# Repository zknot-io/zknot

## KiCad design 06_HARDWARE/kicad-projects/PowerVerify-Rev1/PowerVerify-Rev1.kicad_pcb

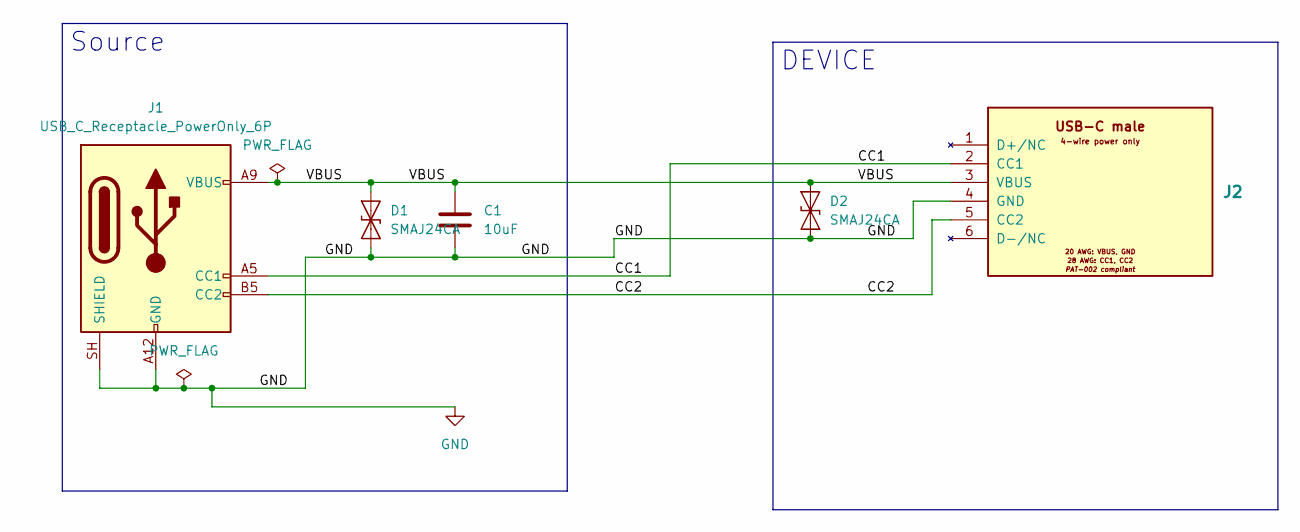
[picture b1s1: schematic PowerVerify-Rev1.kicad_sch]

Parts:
C1: 10uF; C_0805_2012Metric
D1, D2: SMAJ24CA; D_SMA
J1: USB_C_Receptacle_PowerOnly_6P; USB_C_Receptacle_GCT_USB4135-GF-A_6P_TopMnt_Horizontal
J2: Pigtail_USB-C_4wire_ZKNOT; Pigtail_USB-C_4wire_6pad_ZKNOT_THT_Arc; MPN ZKNOT-PGT-USB-C-4W-20AWG-R1

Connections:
/CC1: J1.A5 (CC1), J2.2 (CC1)
/CC2: J1.B5 (CC2), J2.5 (CC2)
/VBUS: C1.2, D1.2 (A2), D2.2 (A2), J1.A9 (VBUS), J1.B9 (VBUS), J2.3 (VBUS)
GND: C1.1, D1.1 (A1), D2.1 (A1), J1.A12 (GND), J1.B12 (GND), J1.SH (SHIELD), J2.4 (GND)

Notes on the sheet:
DEVICE
Source

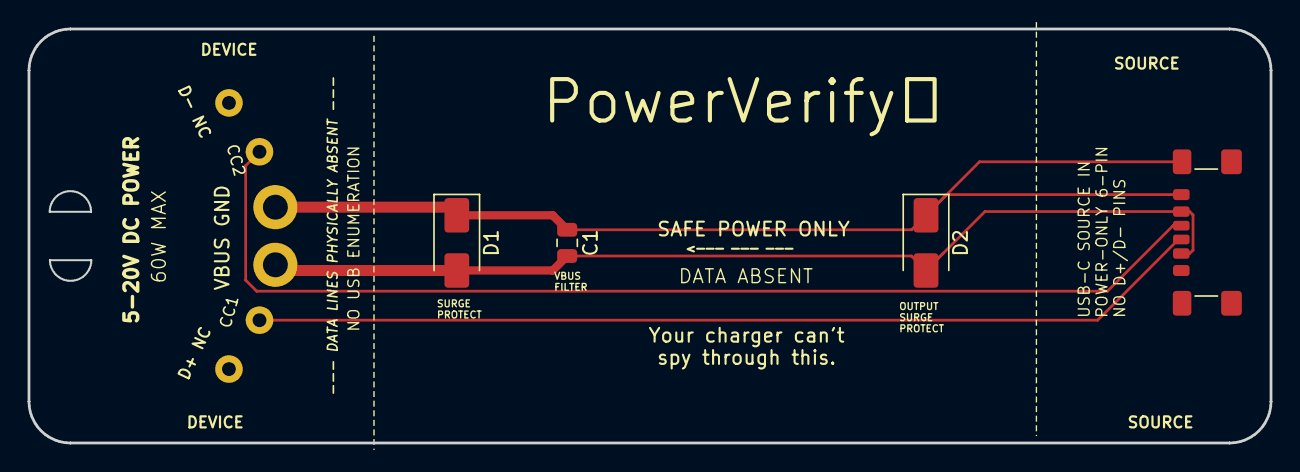
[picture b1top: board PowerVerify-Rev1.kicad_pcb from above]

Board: 2 copper layers, 90.0 x 30.0 mm, 5 parts (0 on the bottom side), 4 nets.

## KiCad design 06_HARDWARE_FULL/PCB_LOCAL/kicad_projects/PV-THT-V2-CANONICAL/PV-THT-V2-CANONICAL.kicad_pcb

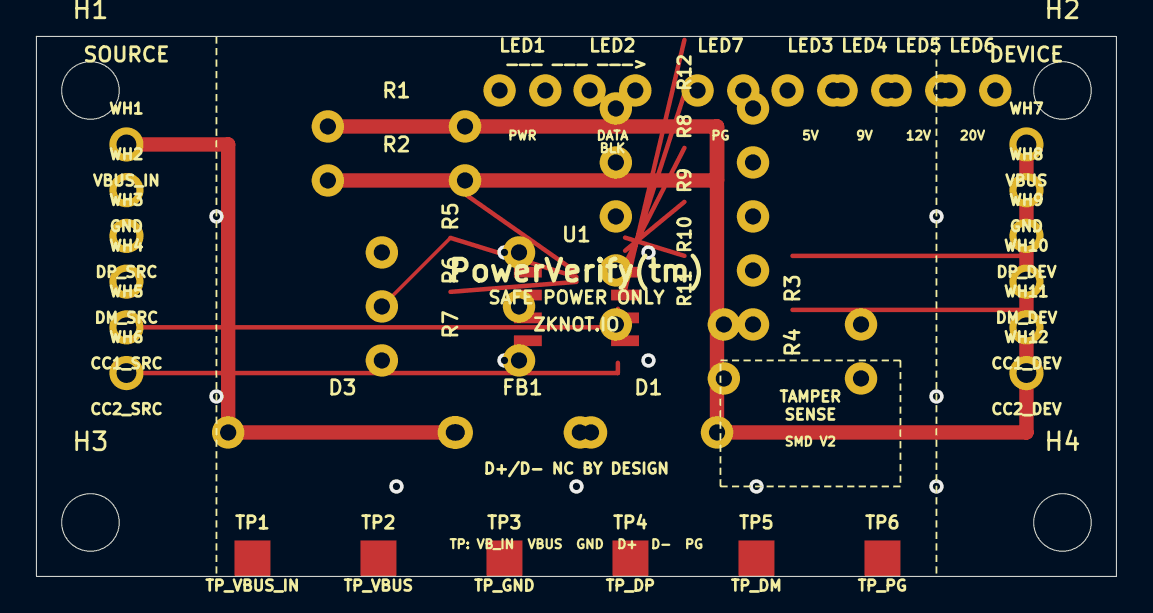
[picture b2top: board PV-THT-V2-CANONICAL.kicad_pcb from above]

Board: 2 copper layers, 60.0 x 30.0 mm, 45 parts (0 on the bottom side), 18 nets.

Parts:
D1: 1N4007; D_DO-41_SOD81_P7.62mm_Horizontal
D3: P6KE5V6A; D_DO-15_P12.70mm_Horizontal
FB1: BLM21PG600SN1D; L_Axial_P7.62mm
H1, H2, H3, H4: MountingHole_M3; MountingHole_3.2mm_M3
LED1: GREEN_PWR; LED_D3.0mm
LED2: RED_DATA_BLK; LED_D3.0mm
LED3: BLUE_5V; LED_D3.0mm
LED4: AMBER_9V; LED_D3.0mm
LED5: ORANGE_12V; LED_D3.0mm
LED6: RED_20V; LED_D3.0mm
LED7: GREEN_PG; LED_D3.0mm
R1, R8, R9, R10, R11, R12: 330; R_Axial_DIN0207_L6.3mm_D2.5mm_P7.62mm_Horizontal
R2: 1k; R_Axial_DIN0207_L6.3mm_D2.5mm_P7.62mm_Horizontal
R3, R4: 5.1k; R_Axial_DIN0207_L6.3mm_D2.5mm_P7.62mm_Horizontal
R5: CFG3_SEL; R_Axial_DIN0207_L6.3mm_D2.5mm_P7.62mm_Horizontal
R6: CFG2_SEL; R_Axial_DIN0207_L6.3mm_D2.5mm_P7.62mm_Horizontal
R7: CFG1_SEL; R_Axial_DIN0207_L6.3mm_D2.5mm_P7.62mm_Horizontal
TP1: TP_VBUS_IN; TestPoint_Pad_2.0x2.0mm
TP2: TP_VBUS; TestPoint_Pad_2.0x2.0mm
TP3: TP_GND; TestPoint_Pad_2.0x2.0mm
TP4: TP_DP; TestPoint_Pad_2.0x2.0mm
TP5: TP_DM; TestPoint_Pad_2.0x2.0mm
TP6: TP_PG; TestPoint_Pad_2.0x2.0mm
U1: CH224K; SOIC-8_3.9x4.9mm_P1.27mm
WH1: VBUS_IN; WireHole_1.1mm
WH2, WH8: GND; WireHole_1.1mm
WH3: DP_SRC; WireHole_1.1mm
WH4: DM_SRC; WireHole_1.1mm
WH5: CC1_SRC; WireHole_1.1mm
WH6: CC2_SRC; WireHole_1.1mm
WH7: VBUS; WireHole_1.1mm
WH9: DP_DEV; WireHole_1.1mm
WH10: DM_DEV; WireHole_1.1mm
WH11: CC1_DEV; WireHole_1.1mm
WH12: CC2_DEV; WireHole_1.1mm

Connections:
CC1_SRC: R3.1, U1.7, WH5.1
CC2_SRC: R4.1, U1.8, WH6.1
CFG1: R7.1, U1.3
CFG2: R6.1, U1.2
CFG3: R5.1, U1.1
DM_SRC: TP5.1, WH4.1
DP_SRC: TP4.1, WH3.1
FLAG_5V: LED3.1, R8.1
FLAG_9V: LED4.1, R9.1
FLAG_12V: LED5.1, R10.1
FLAG_20V: LED6.1, R11.1, U1.6
GND: D3.2, LED1.2, LED2.2, LED3.2, LED4.2, LED5.2, LED6.2, LED7.2, R3.2, R4.2, R5.2, R6.2, R7.2, R8.2, R9.2, R10.2, R11.2, TP3.1, U1.4, WH2.1, WH8.1
LED1_A: LED1.1, R1.2
LED2_A: LED2.1, R2.2
LED7_A: LED7.1, R12.2
PG: R12.1, TP6.1, U1.5
VBUS: D1.2, FB1.2, R1.1, R2.1, TP2.1, WH7.1
VBUS_IN: D1.1, D3.1, FB1.1, TP1.1, WH1.1

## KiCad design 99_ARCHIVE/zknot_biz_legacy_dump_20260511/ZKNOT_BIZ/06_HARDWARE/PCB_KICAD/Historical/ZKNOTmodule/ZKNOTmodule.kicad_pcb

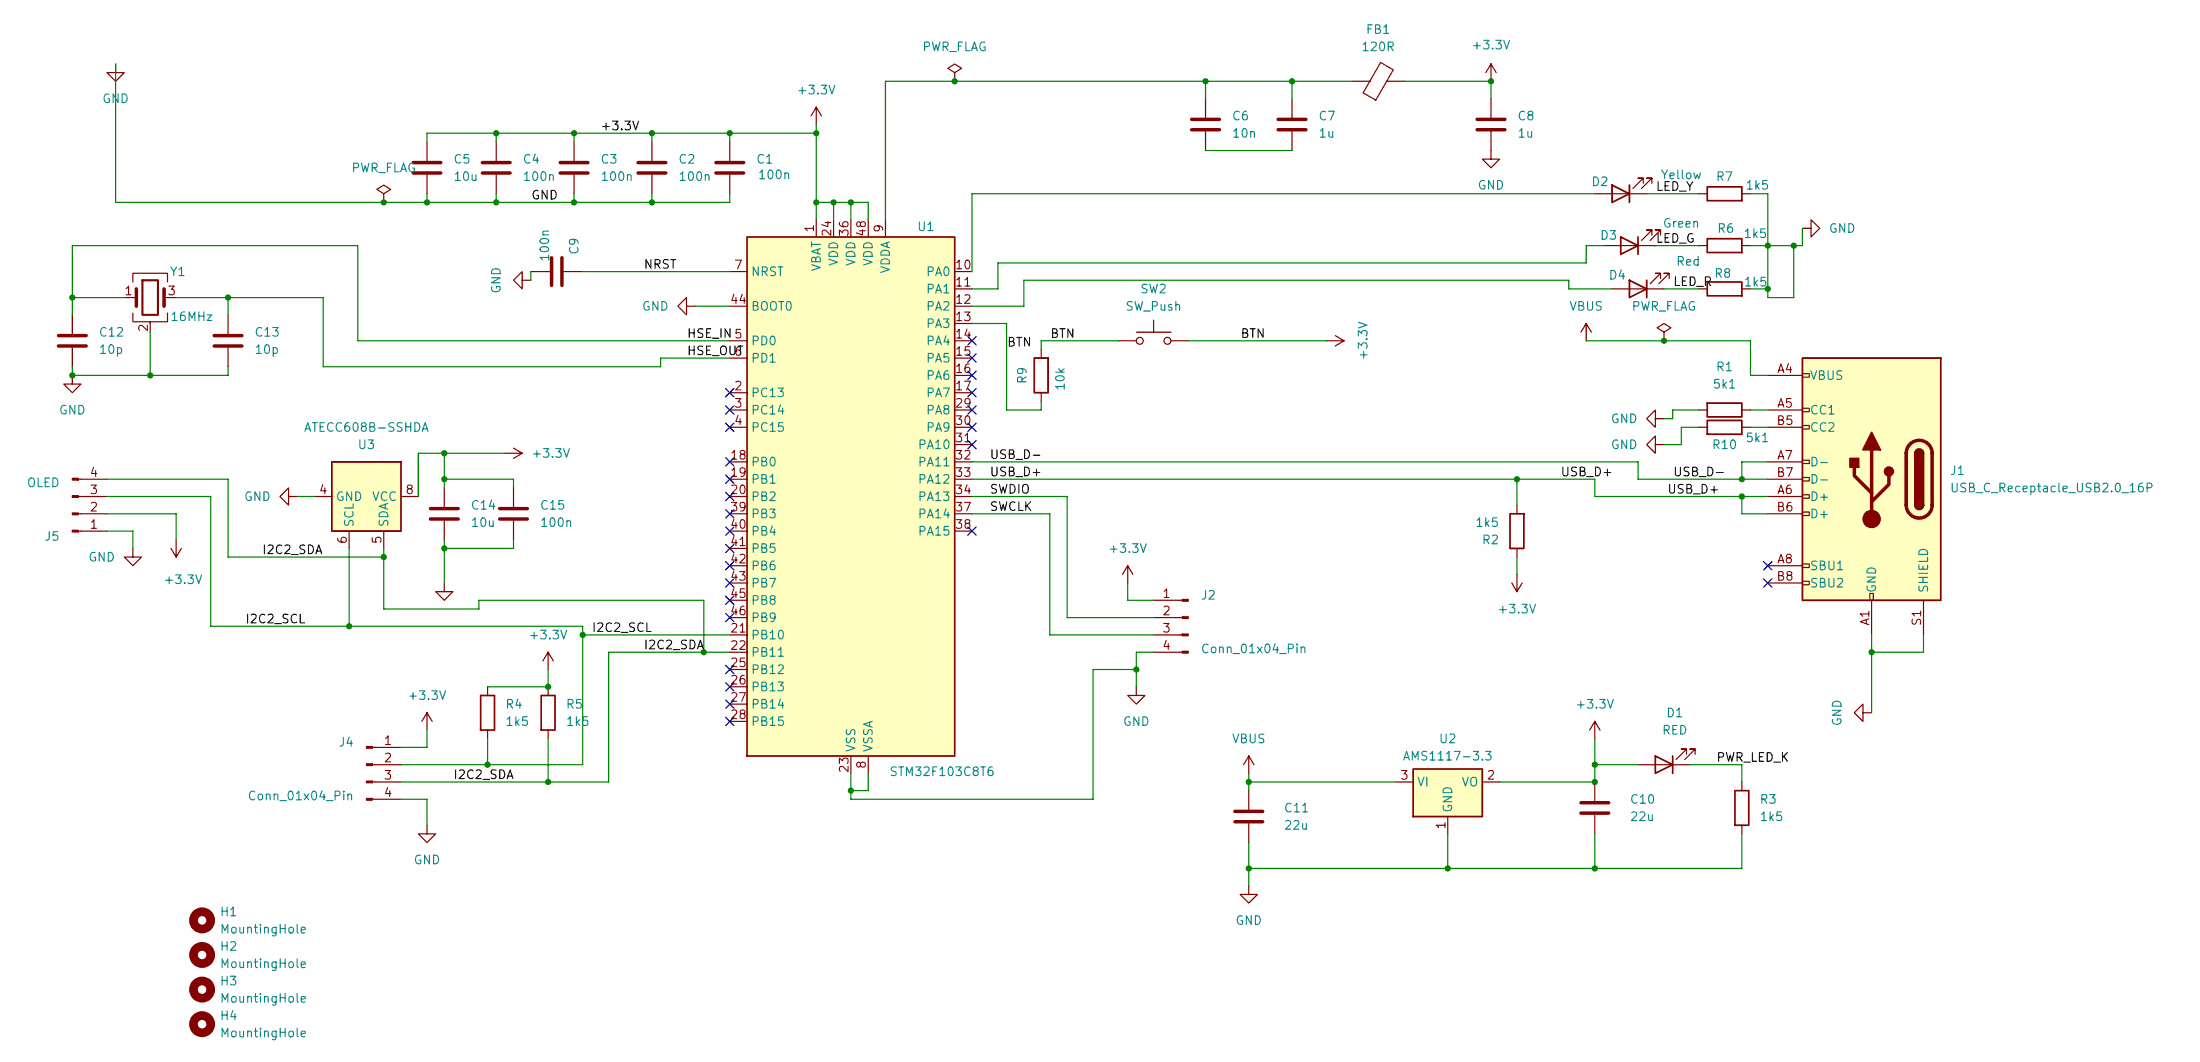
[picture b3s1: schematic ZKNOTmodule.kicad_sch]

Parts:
C1, C2, C3, C4, C9, C15: 100n; C_0805_2012Metric
C5, C14: 10u; C_0805_2012Metric
C6: 10n; C_0805_2012Metric
C7, C8: 1u; C_0805_2012Metric
C10, C11: 22u; C_0805_2012Metric
C12, C13: 10p; C_0805_2012Metric
D1: RED; LED_0805_2012Metric
D2: Yellow; LED_0805_2012Metric
D3: Green; LED_0805_2012Metric
D4: Red; LED_0805_2012Metric
FB1: 120R; L_0805_2012Metric
H1: MountingHole; MountingHole_4.3x6.2mm_M4_Pad
H2, H3, H4: MountingHole; MountingHole_2.2mm_M2
J1: USB_C_Receptacle_USB2.0_16P; USB_C_Receptacle_HCTL_HC-TYPE-C-16P-01A
J2, J4: Conn_01x04_Pin; PinHeader_1x04_P2.54mm_Vertical
J5: OLED; PinHeader_1x04_P2.54mm_Vertical
R1, R10: 5k1; R_0805_2012Metric
R2, R3, R4, R5, R6, R7, R8: 1k5; R_0805_2012Metric
R9: 10k; R_0805_2012Metric
SW2: SW_Push; SW_SPST_TL3342
U1: STM32F103C8T6; LQFP-48_7x7mm_P0.5mm
U2: AMS1117-3.3; SOT-223-3_TabPin2
U3: ATECC608B-SSHDA; SOIC-8_3.9x4.9mm_P1.27mm
Y1: 16MHz; Crystal_SMD_3225-4Pin_3.2x2.5mm

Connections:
+3.3V: C1.1, C2.1, C3.1, C4.1, C5.1, C8.1, C10.1, C14.1, C15.1, D1.2 (A), FB1.2, J2.1, J4.1, J5.2, R2.1, R4.1, R5.1, R9.1, R9.2, SW2.1, SW2.2, U1.1 (VBAT), U1.13 (PA3), U1.24 (VDD), U1.36 (VDD), U1.48 (VDD), U2.2 (VO), U3.8 (VCC)
/HSE_IN: C12.1, U1.5 (PD0), Y1.1
/HSE_OUT: C13.1, U1.6 (PD1), Y1.3
/I2C2_SCL: J4.2, J5.3, R4.2, U1.21 (PB10), U3.6 (SCL)
/I2C2_SDA: J4.3, J5.4, R5.2, U1.22 (PB11), U3.5 (SDA)
/LED_G: D3.1 (K), R6.1
/LED_R: D4.1 (K), R8.1
/LED_Y: D2.1 (K), R7.1
/NRST: C9.1, U1.7 (NRST)
/PWR_LED_K: D1.1 (K), R3.1
/SWCLK: J2.3, U1.37 (PA14)
/SWDIO: J2.2, U1.34 (PA13)
/USB_D+: J1.A6 (D+), J1.B6 (D+), R2.2, U1.33 (PA12)
/USB_D-: J1.A7 (D-), J1.B7 (D-), U1.32 (PA11)
GND: C1.2, C2.2, C3.2, C4.2, C5.2, C8.2, C9.2, C10.2, C11.2, C12.2, C13.2, C14.2, C15.2, J1.A1 (GND), J1.A12 (GND), J1.B1 (GND), J1.B12 (GND), J1.S1 (SHIELD), J2.4, J4.4, J5.1, R1.2, R3.2, R6.2, R7.2, R8.2, R10.2, U1.8 (VSSA), U1.23 (VSS), U1.35 (VSS), U1.44 (BOOT0), U1.47 (VSS), U2.1 (GND), U3.4 (GND), Y1.2 (G), Y1.4 (G)
unnamed: C6.2, C7.2
unnamed: D2.2 (A), U1.10 (PA0)
unnamed: D3.2 (A), U1.11 (PA1)
unnamed: D4.2 (A), U1.12 (PA2)
unnamed: J1.A5 (CC1), R1.1
unnamed: J1.B5 (CC2), R10.1
unnamed: C6.1, C7.1, FB1.1, U1.9 (VDDA)
VBUS: C11.1, J1.A4 (VBUS), J1.A9 (VBUS), J1.B4 (VBUS), J1.B9 (VBUS), U2.3 (VI)

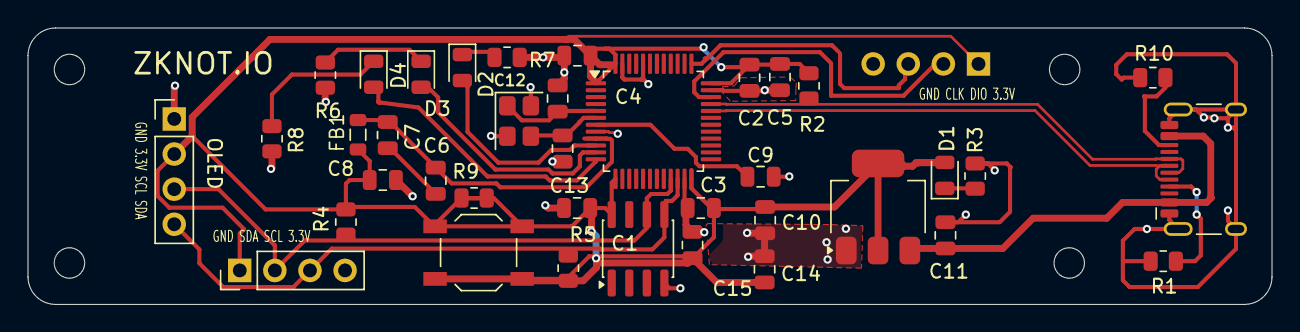
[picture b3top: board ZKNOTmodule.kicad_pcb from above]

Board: 2 copper layers, 90.0 x 20.0 mm, 43 parts (1 on the bottom side), 23 nets.

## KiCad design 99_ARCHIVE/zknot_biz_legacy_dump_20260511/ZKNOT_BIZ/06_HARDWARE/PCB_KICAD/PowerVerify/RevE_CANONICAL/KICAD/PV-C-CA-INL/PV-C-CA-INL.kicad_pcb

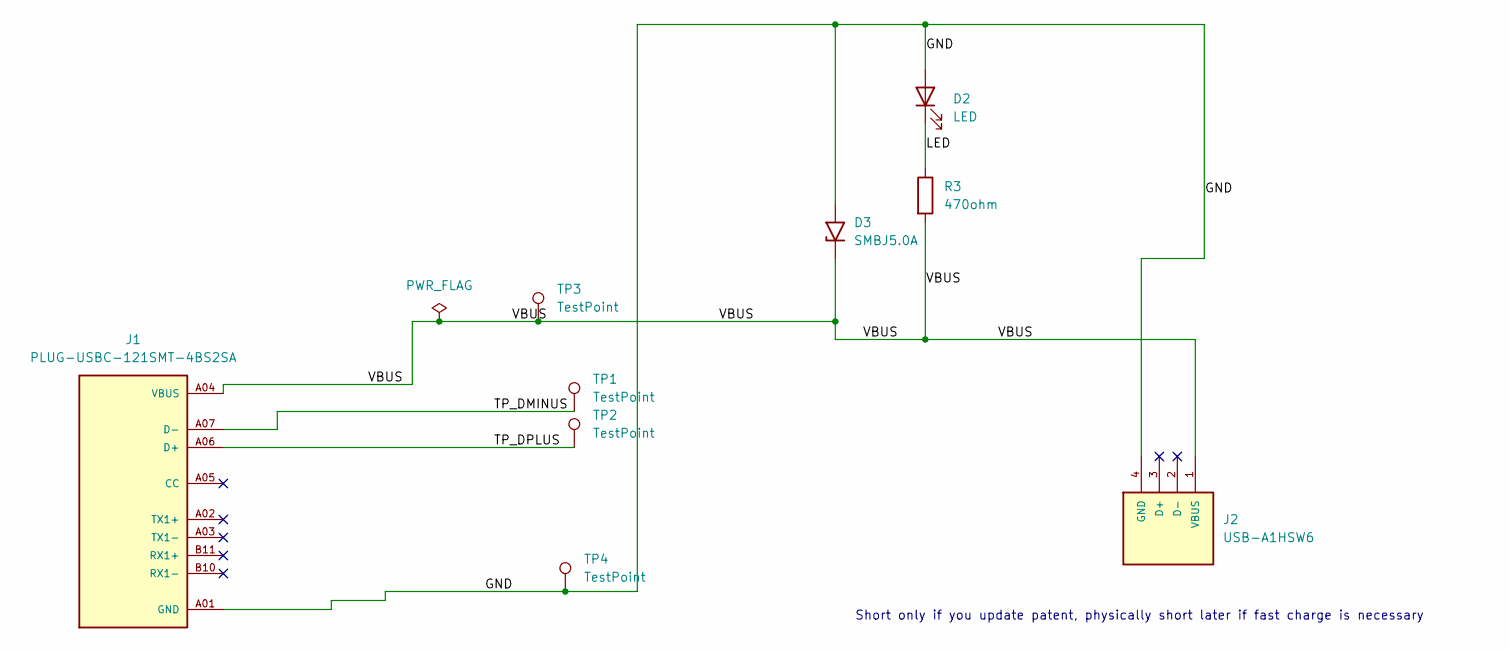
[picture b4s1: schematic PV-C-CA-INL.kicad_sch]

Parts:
D2: LED; LED_0603_1608Metric
D3: SMBJ5.0A; D_SMB
J1: PLUG-USBC-121SMT-4BS2SA; GLOBTEK_PLUG-USBC-121SMT-4BS2SA; PARTREV A1; DigiKey_Part_Number 1939-PLUG-USBC-121SMT-4BS2SACT-ND
J2: USB-A1HSW6; OST_USB-A1HSW6; PARTREV A; DigiKey_Part_Number ED2989-ND
R3: 470ohm; R_0402_1005Metric
TP1, TP2, TP3, TP4: TestPoint; TestPoint_Pad_D1.5mm

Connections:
/LED: D2.1 (K), R3.1
/TP_DMINUS: J1.A07 (D-), TP1.1
/TP_DPLUS: J1.A06 (D+), TP2.1
GND: D2.2 (A), D3.2 (A2), J1.A01 (GND), J1.A12 (GND), J1.B12 (GND), J1.G1 (GND), J1.G2 (GND), J2.4 (GND), TP4.1
unnamed: J2.2 (D-), J2.3 (D+)
VBUS: D3.1 (A1), J1.A04 (VBUS), J1.B09 (VBUS), J2.1 (VBUS), R3.2, TP3.1

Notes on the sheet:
Short only if you update patent, physically short later if fast charge is necessary

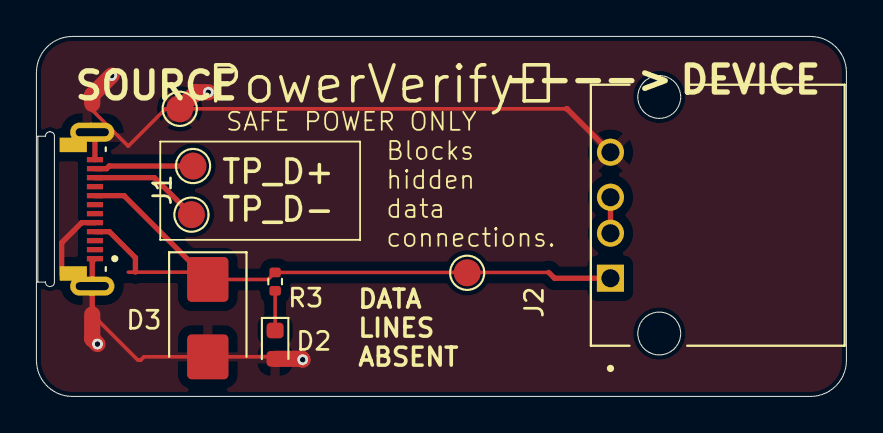
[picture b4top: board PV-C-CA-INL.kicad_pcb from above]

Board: 2 copper layers, 45.0 x 20.0 mm, 9 parts (0 on the bottom side), 6 nets.

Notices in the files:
06_HARDWARE/kicad-projects/PowerVerify-Rev1/PowerVerify-Rev1.kicad_pcb:
PAT-002 © 2026
